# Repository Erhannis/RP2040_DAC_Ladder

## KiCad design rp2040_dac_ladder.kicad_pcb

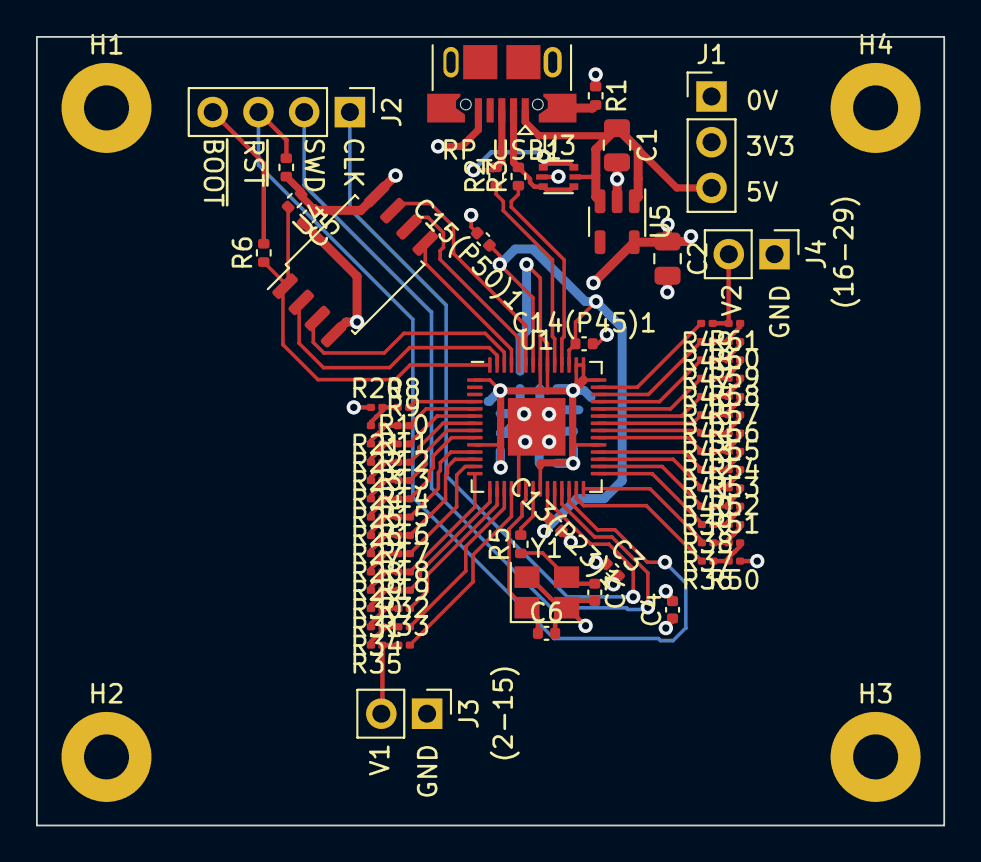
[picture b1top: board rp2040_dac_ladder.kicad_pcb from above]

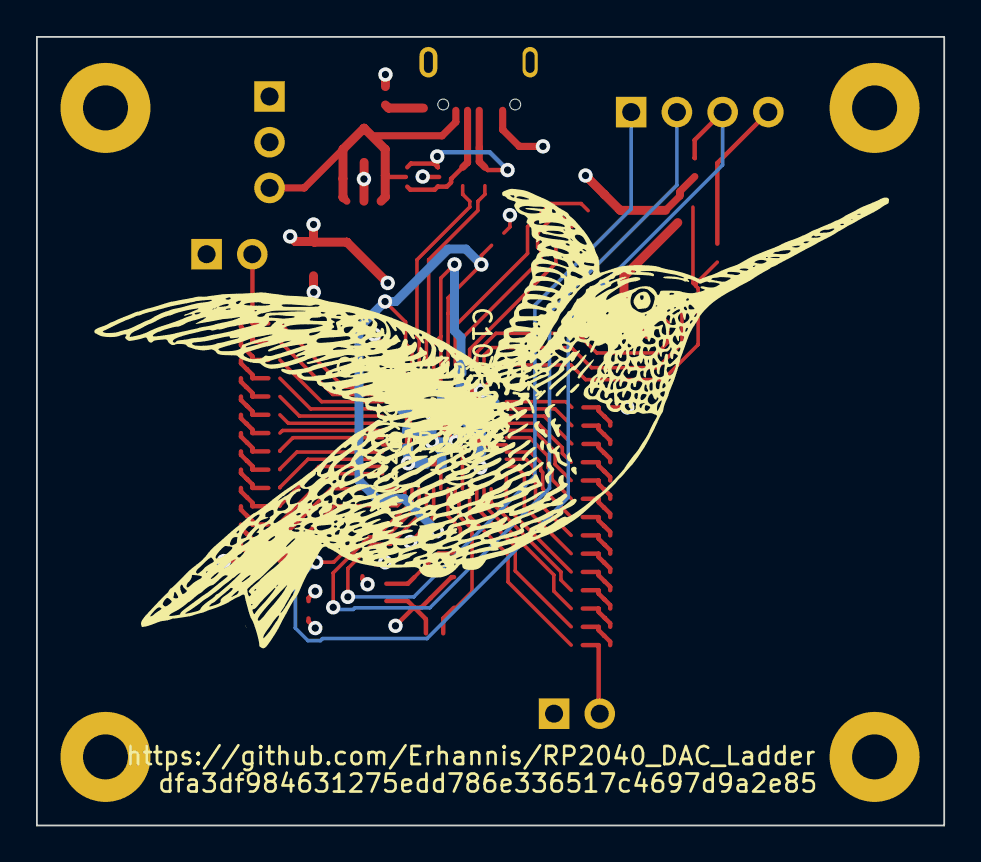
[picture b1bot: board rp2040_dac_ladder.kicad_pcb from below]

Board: 4 copper layers, 50.4 x 43.8 mm, 94 parts (7 on the bottom side), 78 nets.

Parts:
C1, C2: 10uF; C_0805_2012Metric
C3, C4, C5, C6(P10)1, C7(P1)1, C8(P22)1, C9(P42)1, C10(P49)1, C12(P33)1, C13(P23)1, C15(P50)1: 100nF; C_0402_1005Metric
C6, C7: 35pF; C_0402_1005Metric
C11(P43n44)1, C14(P45)1: 1uF; C_0402_1005Metric
H1, H2, H3, H4: MountingHole_Pad; MountingHole_2.5mm_Pad
J1: Conn_01x03_Pin; PinHeader_1x03_P2.54mm_Vertical
J2: Conn_01x04_Pin; PinHeader_1x04_P2.54mm_Vertical
J3, J4: Conn_01x02_Pin; PinHeader_1x02_P2.54mm_Vertical
R1: 1M; R_0402_1005Metric
R2, R3: 27; R_0402_1005Metric
R4, R7: 10K; R_0402_1005Metric
R5: 1K; R_0402_1005Metric
R6: 1k; R_0402_1005Metric
R8, R9, R10, R11, R12, R13, R14, R15, R16, R17, R18, R19, R20, R32, R33, R36, R37, R38, R39, R40, R41, R42, R43, R44, R45, R46, R47, R48, R49, R50: 1k; R_0201_0603Metric
R21, R22, R23, R24, R25, R26, R27, R28, R29, R30, R31, R34, R35, R51, R52, R53, R54, R55, R56, R57, R58, R59, R60, R61, R62, R63: 499; R_0201_0603Metric
RP_USB1: USB_B_Micro; USB_Micro-B_XKB_U254-051T-4BH83-F1S
U1: RP2040; QFN-56-1EP_7x7mm_P0.4mm_EP3.2x3.2mm
U3: USBLC6-2P6; SOT-666
U4: W25Q128JVS; SOIC-8_5.23x5.23mm_P1.27mm
U5: AP2112K-3.3; SOT-23-5
Y1: 12MHz; Crystal_SMD_3225-4Pin_3.2x2.5mm

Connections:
+1V2: C13(P23)1.1, C14(P45)1.1, C15(P50)1.1, U1.23 (DVDD), U1.45 (VREG_VOUT), U1.50 (DVDD)
+3V3: C2.1, C3.1, C4.1, C5.1, C6(P10)1.1, C7(P1)1.1, C8(P22)1.1, C9(P42)1.1, C10(P49)1.1, C11(P43n44)1.1, C12(P33)1.1, J1.2, R4.1, R7.2, U1.1 (IOVDD), U1.10 (IOVDD), U1.22 (IOVDD), U1.33 (IOVDD), U1.42 (IOVDD), U1.43 (ADC_AVDD), U1.44 (VREG_IN), U1.48 (USB_VDD), U1.49 (IOVDD), U4.8 (VCC), U5.5 (VOUT)
+5V: C1.1, J1.3, RP_USB1.1 (VBUS), U3.5 (VBUS), U5.1 (VIN), U5.3 (EN)
/DAC1_OUT: J3.2, R33.1, R35.1
/DAC2_OUT: J4.2, R49.1, R63.1
/QSPI_CS: R6.1, R7.1, U1.56 (QSPI_SS), U4.1 (~CS)
/QSPI_DATA[0]: U1.53 (QSPI_SD0), U4.5 (DI(IO0))
/QSPI_DATA[1]: U1.55 (QSPI_SD1), U4.2 (DO(IO1))
/QSPI_DATA[2]: U1.54 (QSPI_SD2), U4.3 (IO2)
/QSPI_DATA[3]: U1.51 (QSPI_SD3), U4.7 (IO3)
/QSPI_SCK: U1.52 (QSPI_SCLK), U4.6 (CLK)
/RP_SWCLK: J2.1, U1.24 (SWCLK)
/RP_SWD: J2.2, U1.25 (SWD)
/RP_UD+: R2.1, U1.47 (USB_DP)
/RP_UD-: R3.1, U1.46 (USB_DM)
/USB_BOOT: J2.4, R6.2
/~RESET: J2.3, R4.2, U1.26 (RUN)
GND: C1.2, C2.2, C3.2, C4.2, C5.2, C6.2, C6(P10)1.2, C7.2, C7(P1)1.2, C8(P22)1.2, C9(P42)1.2, C10(P49)1.2, C11(P43n44)1.2, C12(P33)1.2, C13(P23)1.2, C14(P45)1.2, C15(P50)1.2, H1.1, H2.1, H3.1, H4.1, J1.1, J3.1, J4.1, R1.1, R20.1, R50.1, RP_USB1.5 (GND), U1.19 (TESTEN), U1.57 (GND), U3.2 (GND), U4.4 (GND), U5.2 (GND), Y1.2, Y1.4
unnamed: C7.1, R5.1, Y1.3
unnamed: R10.1, R22.1, R23.2
unnamed: R11.1, R23.1, R24.2
unnamed: R12.1, R24.1, R25.2
unnamed: R13.1, R25.1, R26.2
unnamed: R14.1, R26.1, R27.2
unnamed: R15.1, R27.1, R28.2
unnamed: R16.1, R28.1, R29.2
unnamed: R17.1, R29.1, R30.2
unnamed: R18.1, R30.1, R31.2
unnamed: R19.1, R31.1, R34.2
unnamed: R8.1, R20.2, R21.2
unnamed: R9.1, R21.1, R22.2
unnamed: R32.1, R34.1, R35.2
unnamed: R36.1, R50.2, R51.2
unnamed: R37.1, R51.1, R52.2
unnamed: R38.1, R52.1, R53.2
unnamed: R39.1, R53.1, R54.2
unnamed: R40.1, R54.1, R55.2
unnamed: R41.1, R55.1, R56.2
unnamed: R42.1, R56.1, R57.2
unnamed: R43.1, R57.1, R58.2
unnamed: R44.1, R58.1, R59.2
unnamed: R45.1, R59.1, R60.2
unnamed: R46.1, R60.1, R61.2
unnamed: R47.1, R61.1, R62.2
unnamed: R48.1, R62.1, R63.2
unnamed: R2.2, RP_USB1.3 (D+), U3.1 (I/O1), U3.6 (I/O1)
unnamed: R3.2, RP_USB1.2 (D-), U3.3 (I/O2), U3.4 (I/O2)
unnamed: R1.2, RP_USB1.6 (Shield)
unnamed: R8.2, U1.4 (GPIO2)
unnamed: R9.2, U1.5 (GPIO3)
unnamed: R10.2, U1.6 (GPIO4)
unnamed: R11.2, U1.7 (GPIO5)
unnamed: R12.2, U1.8 (GPIO6)
unnamed: R13.2, U1.9 (GPIO7)
unnamed: R14.2, U1.11 (GPIO8)
unnamed: R15.2, U1.12 (GPIO9)
unnamed: R16.2, U1.13 (GPIO10)
unnamed: R17.2, U1.14 (GPIO11)
unnamed: R18.2, U1.15 (GPIO12)
unnamed: R19.2, U1.16 (GPIO13)
unnamed: R32.2, U1.17 (GPIO14)
unnamed: R33.2, U1.18 (GPIO15)
unnamed: R36.2, U1.27 (GPIO16)
unnamed: R37.2, U1.28 (GPIO17)
unnamed: R38.2, U1.29 (GPIO18)
unnamed: R39.2, U1.30 (GPIO19)
unnamed: R40.2, U1.31 (GPIO20)
unnamed: R41.2, U1.32 (GPIO21)
unnamed: R42.2, U1.34 (GPIO22)
unnamed: R43.2, U1.35 (GPIO23)
unnamed: R44.2, U1.36 (GPIO24)
unnamed: R45.2, U1.37 (GPIO25)
unnamed: R46.2, U1.38 (GPIO26_ADC0)
unnamed: R47.2, U1.39 (GPIO27_ADC1)
unnamed: R48.2, U1.40 (GPIO28_ADC2)
unnamed: R49.2, U1.41 (GPIO29_ADC3)
unnamed: C6.1, U1.20 (XIN), Y1.1
unnamed: R5.2, U1.21 (XOUT)

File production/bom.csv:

Designator,Footprint,Quantity,Value,LCSC Part #
"C1, C2",0805,2,10uF,C1713
"C10(P49)1, C12(P33)1, C13(P23)1, C15(P50)1, C3, C4, C5, C6(P10)1, C7(P1)1, C8(P22)1, C9(P42)1",0402,11,100nF,C1525
"C11(P43n44)1, C14(P45)1",0402,2,1uF,C14445
"C6, C7",0402,2,35pF,C415391
"H1, H2, H3, H4",MountingHole_2.5mm_Pad,4,MountingHole_Pad,
J1,PinHeader_1x03_P2.54mm_Vertical,1,Conn_01x03_Pin,C429954
J2,PinHeader_1x04_P2.54mm_Vertical,1,Conn_01x04_Pin,C2691448
"J3, J4",PinHeader_1x02_P2.54mm_Vertical,2,Conn_01x02_Pin,C2905434
R1,0402,1,1M,C2906900
"R10, R11, R12, R13, R14, R15, R16, R17, R18, R19, R20, R32, R33, R36, R37, R38, R39, R40, R41, R42, R43, R44, R45, R46, R47, R48, R49, R50, R8, R9",0201,30,1k,C138165
"R2, R3",0402,2,27,C25100
"R21, R22, R23, R24, R25, R26, R27, R28, R29, R30, R31, R34, R35, R51, R52, R53, R54, R55, R56, R57, R58, R59, R60, R61, R62, R63",0201,26,499,C166172
"R4, R7",0402,2,10K,C60490
"R5, R6",0402,2,1K,C140196
RP_USB1,USB_Micro-B_XKB_U254-051T-4BH83-F1S,1,USB_B_Micro,C319160
U1,QFN-56-1EP_7x7mm_P0.4mm_EP3.2x3.2mm,1,RP2040,C2040
U3,SOT-666,1,USBLC6-2P6,C2827693
U4,SOIC-8_5.23x5.23mm_P1.27mm,1,W25Q128JVS,C97521
U5,SOT-23-5,1,AP2112K-3.3,C51118
Y1,Crystal_SMD_3225-4Pin_3.2x2.5mm,1,12MHz,C9002

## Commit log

2023-10-17 Added two 14-bit DAC ladders to schematic
2023-10-17 Switched to 0201 resistors
2023-10-17 Ok, I think I got the dac ladders laid out
2023-10-17 Resized
2023-10-17 Added metadata etc. and submitted for production.
